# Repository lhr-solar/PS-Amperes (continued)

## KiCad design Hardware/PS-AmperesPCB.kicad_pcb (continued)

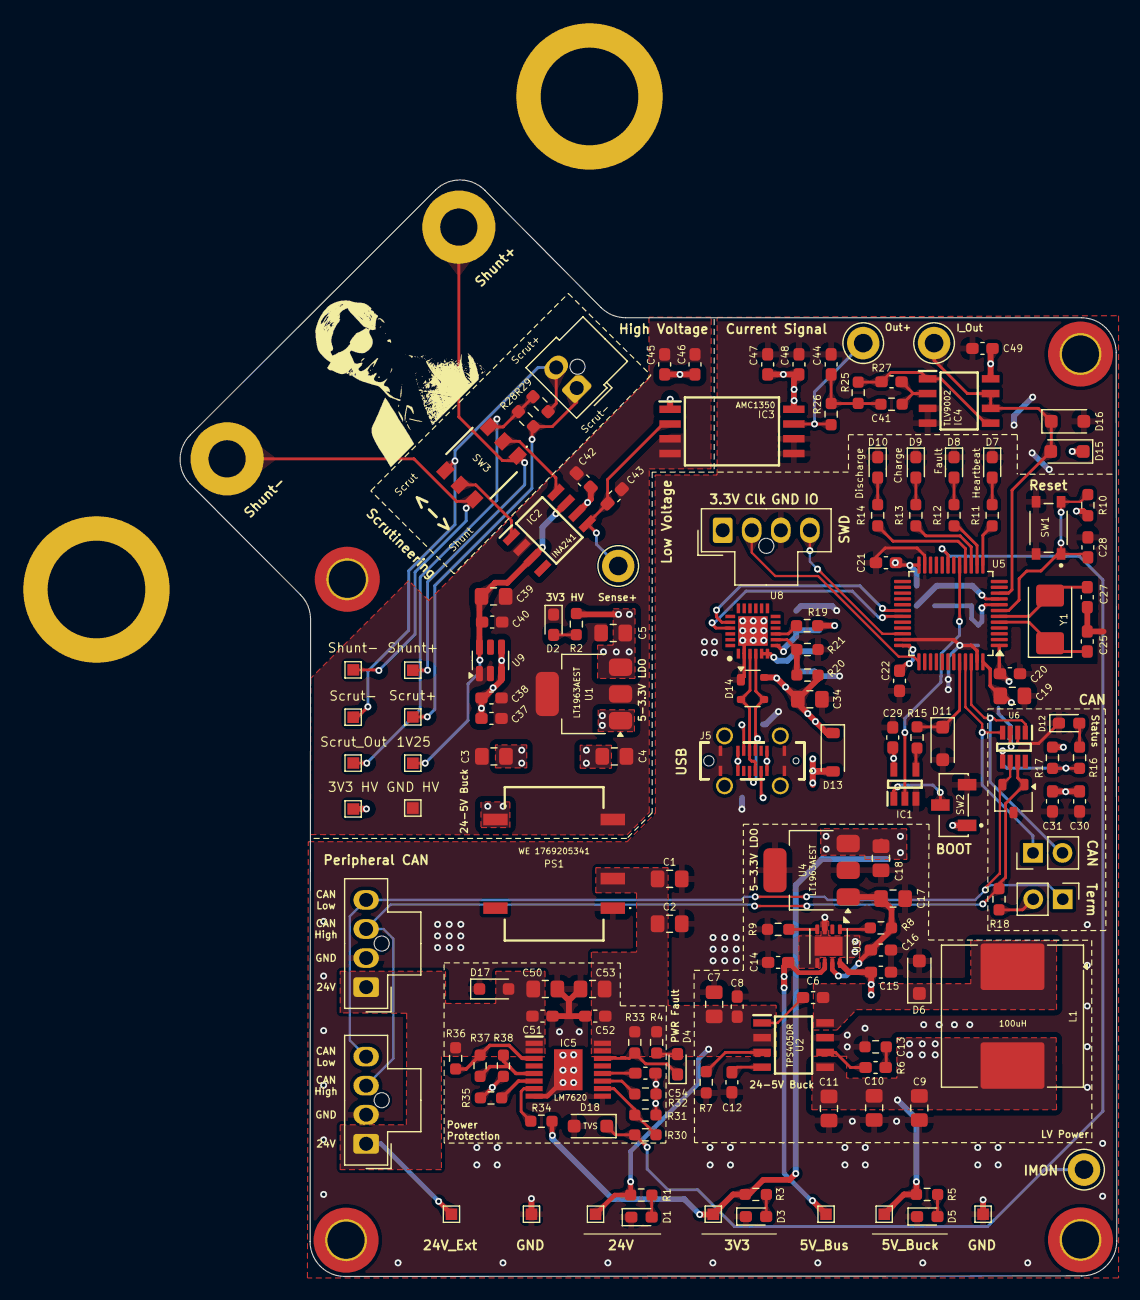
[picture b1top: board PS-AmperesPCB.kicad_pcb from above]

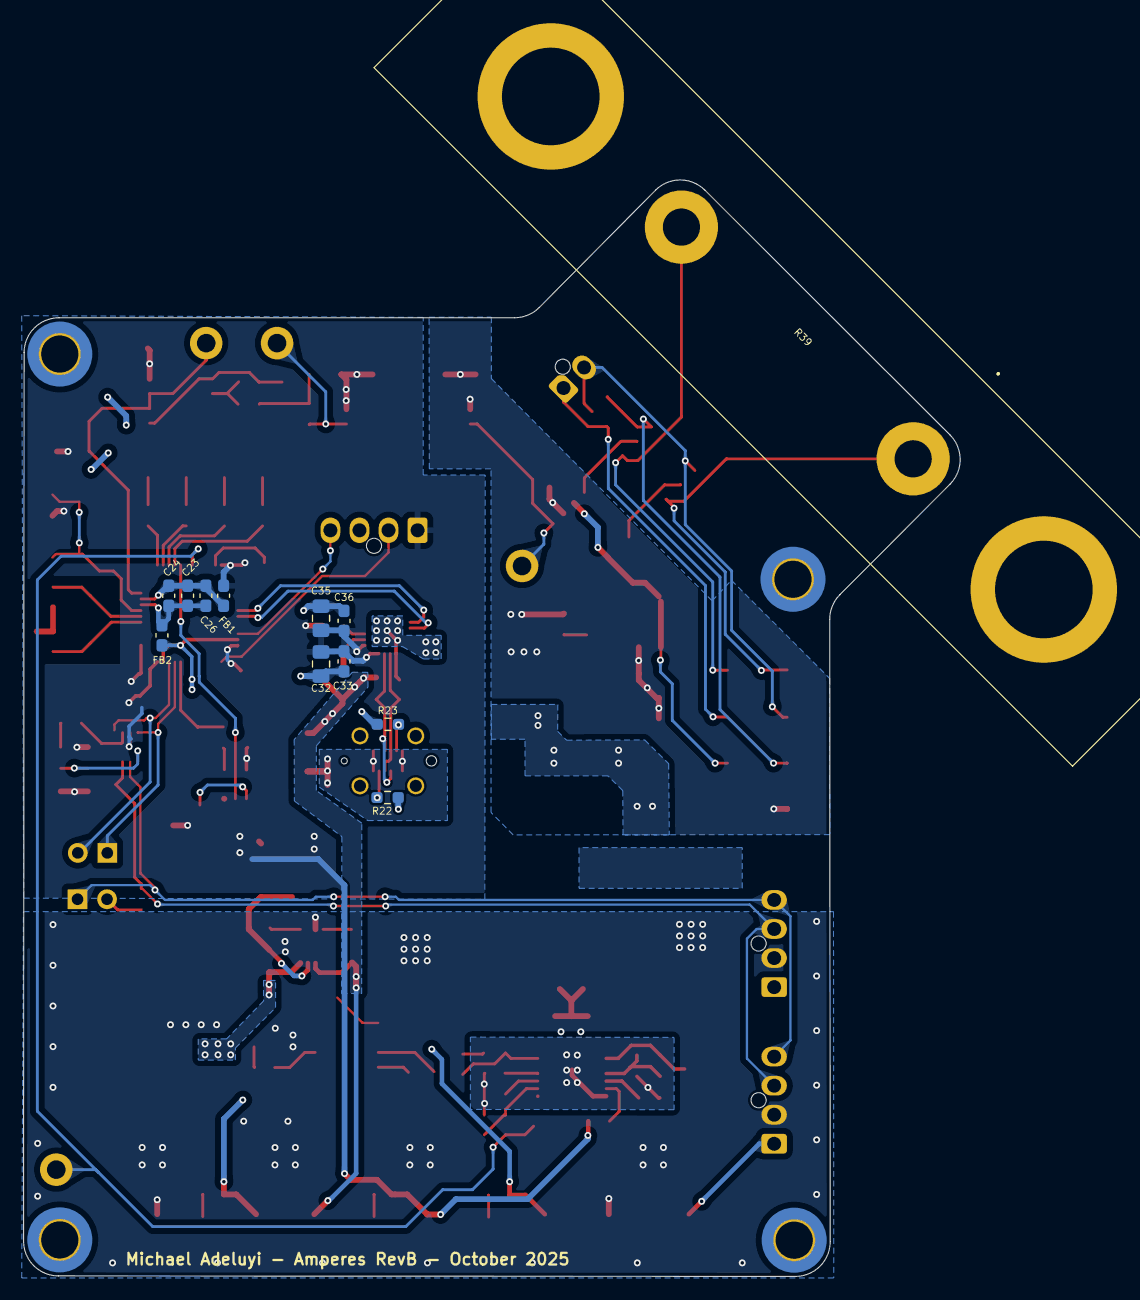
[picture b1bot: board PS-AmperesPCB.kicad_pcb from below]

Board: 2 copper layers, 80.6 x 94.4 mm, 164 parts (13 on the bottom side), 82 nets.

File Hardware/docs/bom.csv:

"Reference","Value","Footprint","Qty","p/n"
"C1,C2,C19,C32,C35","4.7uF","Capacitor_SMD:C_0805_2012Metric_Pad1.18x1.45mm_HandSolder","5",""
"C3,C4,C5,C7,C9,C10,C11,C17,C18,C34,C39,C50,C53","10uF","Capacitor_SMD:C_0805_2012Metric_Pad1.18x1.45mm_HandSolder","13",""
"C6,C14,C15,C29,C33,C36,C37,C40,C42,C49","0.1uF","Capacitor_SMD:C_0603_1608Metric_Pad1.08x0.95mm_HandSolder","10",""
"C8,C16,C38,C41,C46,C47,C51,C52","1uF","Capacitor_SMD:C_0603_1608Metric_Pad1.08x0.95mm_HandSolder","8",""
"C12","10nF","Capacitor_SMD:C_0603_1608Metric_Pad1.08x0.95mm_HandSolder","1",""
"C13","3.3nF","Capacitor_SMD:C_0603_1608Metric_Pad1.08x0.95mm_HandSolder","1",""
"C20,C21,C22,C23,C24,C26,C28,C30,C31,C45,C48,C54","100nF","Capacitor_SMD:C_0603_1608Metric_Pad1.08x0.95mm_HandSolder","12",""
"C25,C27","12p","Capacitor_SMD:C_0603_1608Metric_Pad1.08x0.95mm_HandSolder","2",""
"C43","1nF","Capacitor_SMD:C_0603_1608Metric_Pad1.08x0.95mm_HandSolder","1",""
"C44","7.5uF","Capacitor_SMD:C_0603_1608Metric_Pad1.08x0.95mm_HandSolder","1",""
"D1,TP3","24V","LED_SMD:LED_0603_1608Metric_Pad1.05x0.95mm_HandSolder,TestPoint:TestPoint_Pad_1.0x1.0mm","2",""
"D2","3.3V HV","LED_SMD:LED_0603_1608Metric_Pad1.05x0.95mm_HandSolder","1",""
"D3","3.3V","LED_SMD:LED_0603_1608Metric_Pad1.05x0.95mm_HandSolder","1",""
"D4","PFLT","LED_SMD:LED_0603_1608Metric_Pad1.05x0.95mm_HandSolder","1",""
"D5","BUCK","LED_SMD:LED_0603_1608Metric_Pad1.05x0.95mm_HandSolder","1",""
"D6","MBR230S1F","Diode_SMD:D_SOD-123F","1",""
"D7","Heartbeat","LED_SMD:LED_0603_1608Metric_Pad1.05x0.95mm_HandSolder","1",""
"D8","Fault","LED_SMD:LED_0603_1608Metric_Pad1.05x0.95mm_HandSolder","1",""
"D9","Charge","LED_SMD:LED_0603_1608Metric_Pad1.05x0.95mm_HandSolder","1",""
"D10","Discharge","LED_SMD:LED_0603_1608Metric_Pad1.05x0.95mm_HandSolder","1",""
"D11,D15,D16,D17,D18","TVS","Diode_SMD:D_SOD-123F,Diode_SMD:D_SOD-323_HandSoldering","5",""
"D12","CAN Status","LED_SMD:LED_0603_1608Metric_Pad1.05x0.95mm_HandSolder","1",""
"D13","1N5819HW","Diode_SMD:D_SOD-123","1",""
"D14","SP0503BAHT","Package_TO_SOT_SMD:SOT-143","1",""
"FB1,FB2","FerriteBead","Capacitor_SMD:C_0603_1608Metric_Pad1.08x0.95mm_HandSolder","2",""
"H1","M1","MountingHole:MountingHole_3.2mm_M3_DIN965_Pad_TopBottom","1",""
"H2","M3","MountingHole:MountingHole_3.2mm_M3_DIN965_Pad_TopBottom","1",""
"H3","M2","MountingHole:MountingHole_3.2mm_M3_DIN965_Pad_TopBottom","1",""
"H4","M4","MountingHole:MountingHole_3.2mm_M3_DIN965_Pad_TopBottom","1",""
"IC1","SN74AHC1G32DBVR","Parts:SN74AHC1G32DBVR","1",""
"IC2","INA241A4IDR","Parts:INA241A5IDR","1",""
"IC3","AMC1350DWVR","Parts:AMC1350DWVR","1",""
"IC4","TLV9002QDRQ1","Parts:TLV9002QDRQ1","1",""
"IC5","LM76202QPWPRQ1","UTSVT_Power:LM76202QPWPRQ1","1",""
"J1,J2","PeripheralCAN","UTSVT_Connectors:Molex_Nano-Fit_105309-xx04_1x04_P2.50mm_Vertical","2",""
"J3","SWD","Connector_Molex:Molex_Nano-Fit_105309-xx04_1x04_P2.50mm_Vertical","1",""
"J4","Conn_01x02_Pin","Connector_PinHeader_2.54mm:PinHeader_1x02_P2.54mm_Vertical","1",""
"J5","USB4120-03-C","Parts:USB412003C","1",""
"J6","Scrut Conn","Connector_Molex:Molex_Nano-Fit_105309-xx02_1x02_P2.50mm_Vertical","1",""
"JP1","Termination","Connector_PinHeader_2.54mm:PinHeader_1x02_P2.54mm_Vertical","1",""
"L1","100uH","Inductor_SMD:L_Coilcraft_MSS1246-XXX","1",""
"LOGO1","logo placeholder","UTSVT_Logos:LHRs_LOGO","1",""
"LOGO2","Dr. Hallock","UTSVT_Logos:Hallock_Image_Tiny","1",""
"PS1","1769205341","Parts:WE_1769205341","1",""
"R1,R4,R27","4.3k","Resistor_SMD:R_0603_1608Metric_Pad0.98x0.95mm_HandSolder","3",""
"R2,R3,R11,R12,R13,R14,R16,R18","120","Resistor_SMD:R_0603_1608Metric_Pad0.98x0.95mm_HandSolder","8",""
"R5","768","Resistor_SMD:R_0603_1608Metric_Pad0.98x0.95mm_HandSolder","1",""
"R6","16k","Resistor_SMD:R_0603_1608Metric_Pad0.98x0.95mm_HandSolder","1",""
"R7","ROSC","Resistor_SMD:R_0603_1608Metric_Pad0.98x0.95mm_HandSolder","1",""
"R8,R10,R15,R17,R32,R33,R34","10k","Resistor_SMD:R_0603_1608Metric_Pad0.98x0.95mm_HandSolder","7",""
"R9","332","Resistor_SMD:R_0603_1608Metric_Pad0.98x0.95mm_HandSolder","1",""
"R19","1k","Resistor_SMD:R_0603_1608Metric_Pad0.98x0.95mm_HandSolder","1",""
"R20","22k","Resistor_SMD:R_0603_1608Metric_Pad0.98x0.95mm_HandSolder","1",""
"R21","47k","Resistor_SMD:R_0603_1608Metric_Pad0.98x0.95mm_HandSolder","1",""
"R22,R23","5.1k","Resistor_SMD:R_0603_1608Metric_Pad0.98x0.95mm_HandSolder","2",""
"R25","8.2k","Resistor_SMD:R_0603_1608Metric_Pad0.98x0.95mm_HandSolder","1",""
"R26","3.3k","Resistor_SMD:R_0603_1608Metric_Pad0.98x0.95mm_HandSolder","1",""
"R28","34k","Resistor_SMD:R_0603_1608Metric_Pad0.98x0.95mm_HandSolder","1",""
"R29","51","Resistor_SMD:R_0603_1608Metric_Pad0.98x0.95mm_HandSolder","1",""
"R30","100k","Resistor_SMD:R_0603_1608Metric_Pad0.98x0.95mm_HandSolder","1",""
"R31","19k","Resistor_SMD:R_0603_1608Metric_Pad0.98x0.95mm_HandSolder","1",""
"R35","402k","Resistor_SMD:R_0603_1608Metric_Pad0.98x0.95mm_HandSolder","1",""
"R36","45.3k","Resistor_SMD:R_0603_1608Metric_Pad0.98x0.95mm_HandSolder","1",""
"R37","590","Resistor_SMD:R_0603_1608Metric_Pad0.98x0.95mm_HandSolder","1",""
"R38","2.1k","Resistor_SMD:R_0603_1608Metric_Pad0.98x0.95mm_HandSolder","1",""
"R39","WSBS8518L2500JTP3","Parts:WSBS8518L2500JKM4","1",""
"SW1","RST","Parts:SW_TL3365AF180QG","1",""
"SW2","BOOT","Parts:SW_CJS-1200TA","1",""
"SW3","Scrut Select","Parts:CAS220TB","1",""
"TP1","TP_Current","TestPoint:TestPoint_Keystone_5005-5009_Compact","1",""
"TP2","24V_Ext","TestPoint:TestPoint_Pad_1.0x1.0mm","1",""
"TP4","3V3_HV","TestPoint:TestPoint_Pad_1.0x1.0mm","1",""
"TP5","3V3","TestPoint:TestPoint_Pad_1.0x1.0mm","1",""
"TP6","5V_BK","TestPoint:TestPoint_Pad_1.0x1.0mm","1",""
"TP7","5V_USB","TestPoint:TestPoint_Pad_1.0x1.0mm","1",""
"TP8,TP15","GND","TestPoint:TestPoint_Pad_1.0x1.0mm","2",""
"TP9","GND HV","TestPoint:TestPoint_Pad_1.0x1.0mm","1",""
"TP10","SHUNT+","TestPoint:TestPoint_Pad_1.0x1.0mm","1",""
"TP11","SHUNT-","TestPoint:TestPoint_Pad_1.0x1.0mm","1",""
"TP12","V_In+","TestPoint:TestPoint_Pad_1.0x1.0mm","1",""
"TP13","V_Out+","TestPoint:TestPoint_Pad_1.0x1.0mm","1",""
"TP14","V_In-","TestPoint:TestPoint_Pad_1.0x1.0mm","1",""
"TP16","1V25","TestPoint:TestPoint_Pad_1.0x1.0mm","1",""
"TP17","Sense+","TestPoint:TestPoint_Keystone_5005-5009_Compact","1",""
"TP18","Out+","TestPoint:TestPoint_Keystone_5005-5009_Compact","1",""
"TP19","IMON","TestPoint:TestPoint_Keystone_5005-5009_Compact","1",""
"U1,U4","LT1963AEST-3.3#TRPBF","Package_TO_SOT_SMD:SOT-223-3_TabPin2","2",""
"U2","TPS5405DR","UTSVT_Power:TPS5405DR","1",""
"U3","TPS2115ADRBR","Package_SON:VSON-8-1EP_3x3mm_P0.65mm_EP1.65x2.4mm","1",""
"U5","STM32L431CBTx","Package_QFP:LQFP-48_7x7mm_P0.5mm","1",""
"U6","TCAN337","UTSVT_ICs:TCAN337DCNR","1",""
"U7","CDSOT23-T24CAN","UTSVT_ICs:CDSOT23-T24CAN","1",""
"U8","CP2102N-A02-GQFN24","UTSVT_ICs:CP2102N-A02-GQFN24","1",""
"U9","REF35125QDBVR","Package_TO_SOT_SMD:SOT-23-6","1",""
"Y1","8M","Crystal:Crystal_SMD_Abracon_ABM3-2Pin_5.0x3.2mm","1",""

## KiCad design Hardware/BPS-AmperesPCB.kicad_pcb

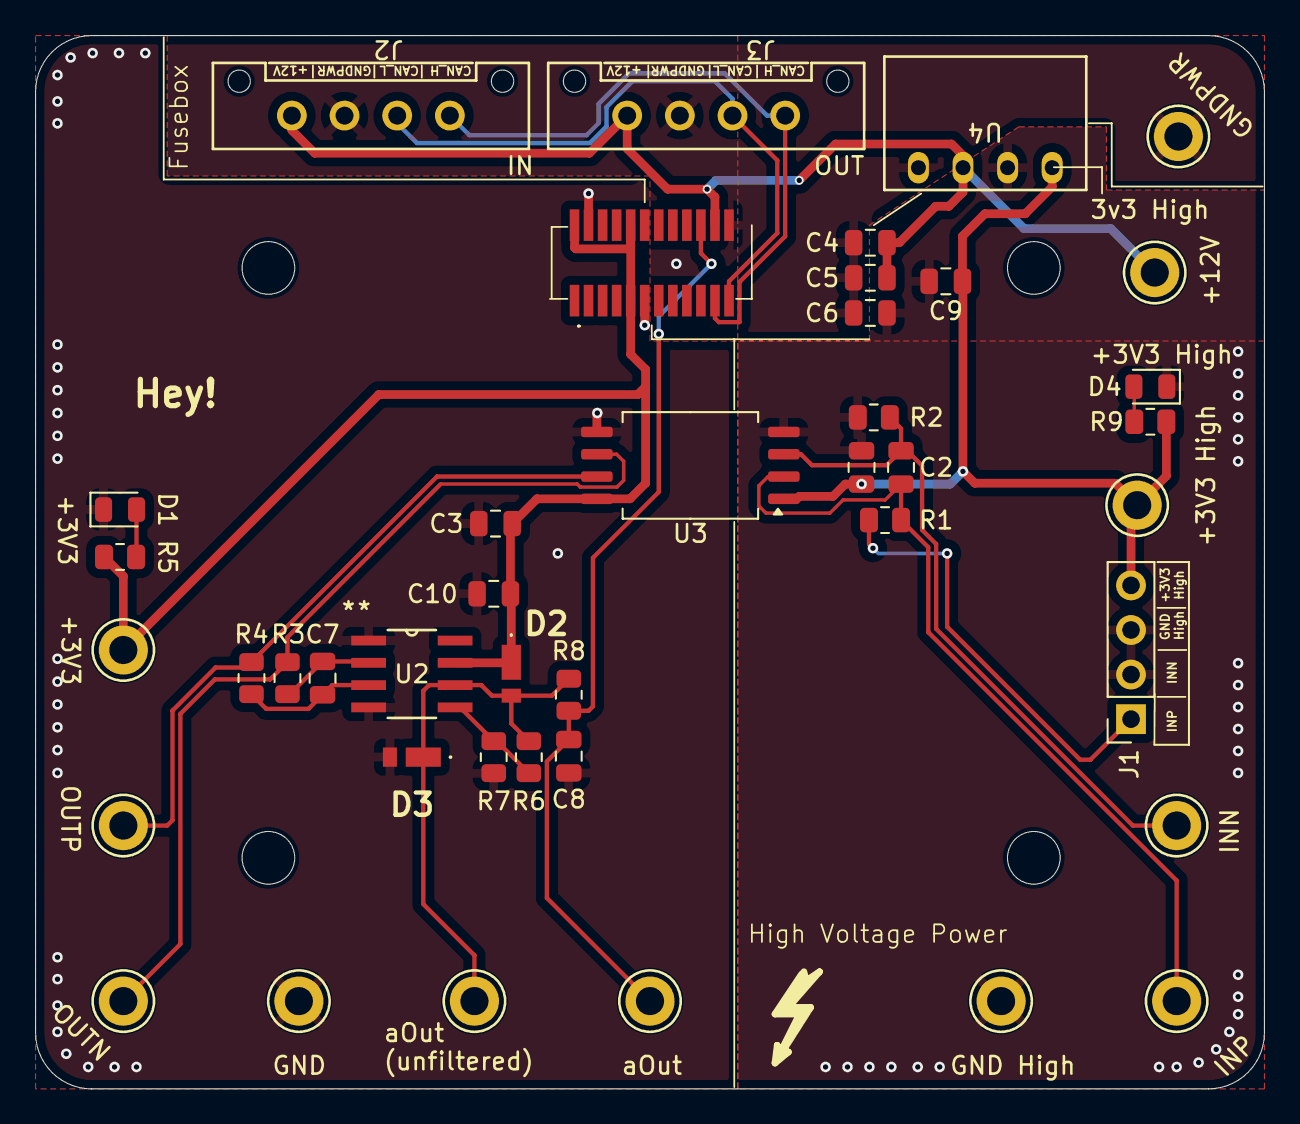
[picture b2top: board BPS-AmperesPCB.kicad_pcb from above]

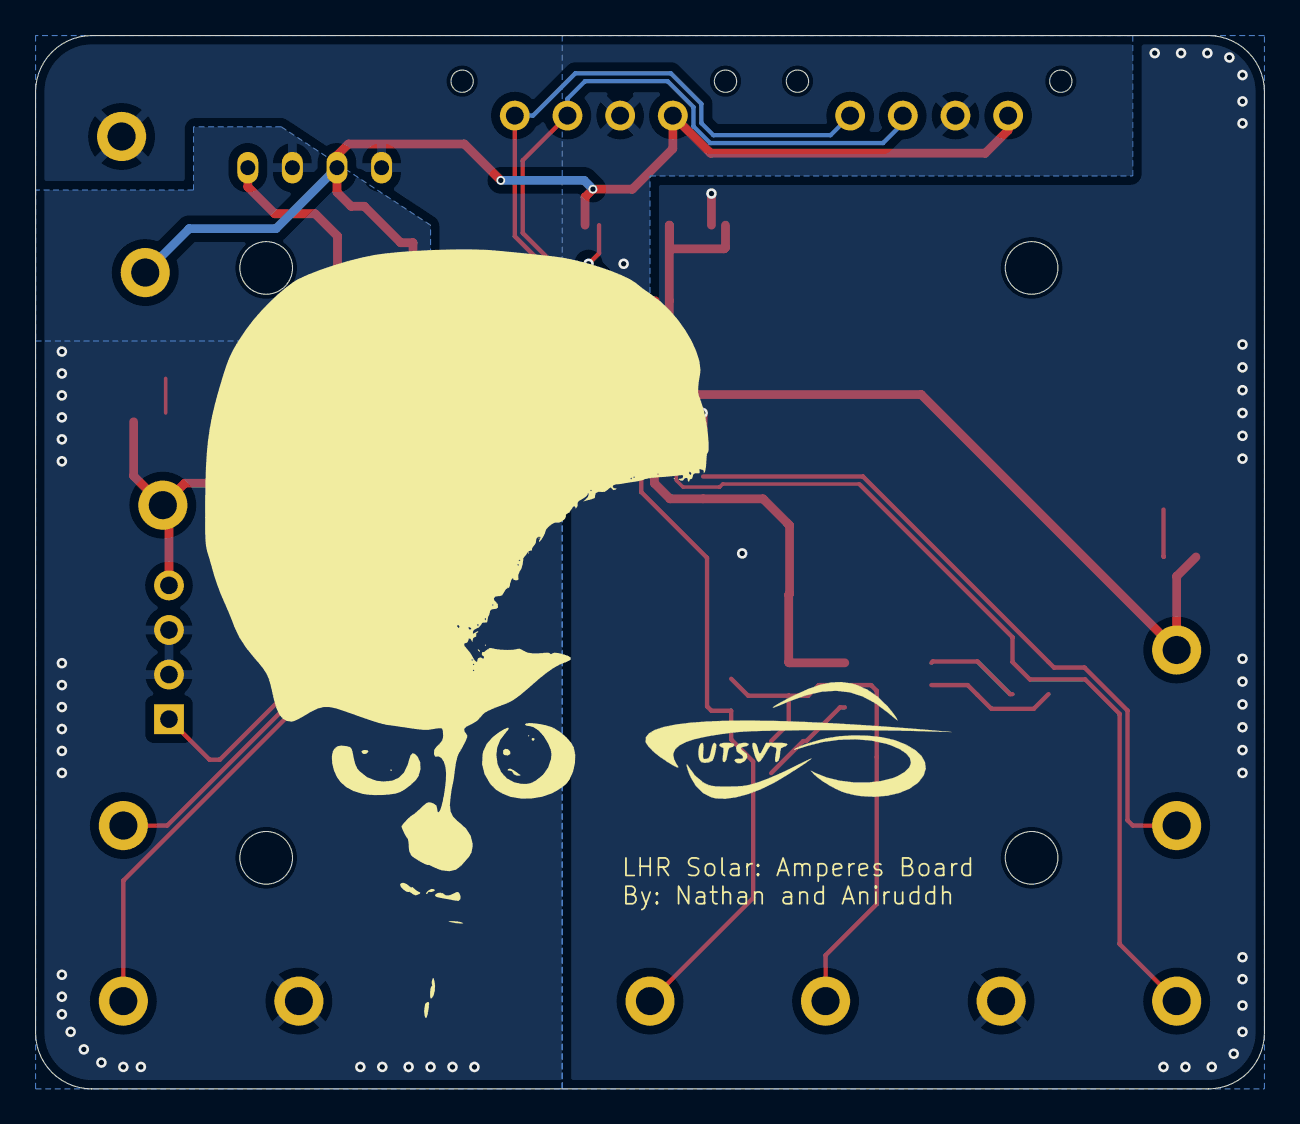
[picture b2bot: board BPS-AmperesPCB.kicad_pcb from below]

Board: 2 copper layers, 70.0 x 60.0 mm, 44 parts (2 on the bottom side), 20 nets.

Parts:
+3V3, +3V3H1, +12V1: TestPoint; TestPoint_Keystone_5005-5009_Compact
C1, C3, C10: 1uF; C_0805_2012Metric
C2, C7, C8: 2.2uF; C_0805_2012Metric
C4: 1n; C_0805_2012Metric
C5: 10u; C_0805_2012Metric
C6: 2.2n; C_0805_2012Metric
C9: 10uF; C_0805_2012Metric
D1, D4: PowerOn; LED_0805_2012Metric
D2, D3: RBE01VYM6AFHTR
GND1: TestPoint; TestPoint_Keystone_5005-5009_Compact
GNDH1: TestPoint; TestPoint_Keystone_5005-5009_Compact
GNDPWR1: TestPoint; TestPoint_Keystone_5005-5009_Compact
INN1: TestPoint; TestPoint_Keystone_5005-5009_Compact
INP1: TestPoint; TestPoint_Keystone_5005-5009_Compact
J1: Conn_01x04; PinSocket_1x04_P2.54mm_Vertical
J2, J3: PeripheralCANConnector; Molex_MicroFit3.0_1x4xP3.00mm_PolarizingPeg_Vertical
LOGO1: aniMegamind
LOGO2: solarlogo; UTSVT_Logo_Symbol
OUTN1: TestPoint; TestPoint_Keystone_5005-5009_Compact
OUTP1: TestPoint; TestPoint_Keystone_5005-5009_Compact
R1, R2, R3, R4: 2.4k; R_0805_2012Metric
R5, R9: 1.5k; R_0805_2012Metric
R6: 12k; R_0805_2012Metric
R7: 1k; R_0805_2012Metric
R8: 4.8k; R_0805_2012Metric
U1: PeripheralSOM
U2: INA145UA/2K5; D8
U3: AMC1300BDWV; SOIC-8_7.5x5.85mm_P1.27mm
U4: RO-123.3S_HP; RI3_DC_Converter
VOut1: TestPoint; TestPoint_Keystone_5005-5009_Compact
aOut1: TestPoint; TestPoint_Keystone_5005-5009_Compact

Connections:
+3V3: +3V3.1, C3.1, C10.1, D2.1 (K), R5.1, U1.2 (+3.3V), U1.9 (+3.3V), U1.10 (VDDA(3.3V)), U2.7 (V+), U3.8 (V+)
+3V3 High: +3V3H1.1, C1.1, C9.1, J1.4, R9.1, U3.1 (V+), U4.4 (+Vout)
+12V: +12V1.1, C4.1, C5.1, J2.1 (12V), J3.1 (12V), U1.22 (+12V_In), U4.2 (+Vin)
/INN: C2.2, INN1.1, R2.1, U3.3 (-)
/INP: C2.1, INP1.1, R1.1, U3.2 (+)
/OUTN: OUTN1.1, R3.2, U3.6 (-)
/OUTP: OUTP1.1, R4.2, U3.7 (+)
/aOut: C8.1, R8.1, U1.20 (PA1(ADC)), aOut1.1
GND: C3.2, C8.2, C10.2, D1.1 (K), D3.2 (A), GND1.1, R7.2, U1.4 (GND), U1.11 (GND), U2.1 (REF), U2.4 (V-), U3.5 (V-)
GND High: C1.2, C6.2, C9.2, D4.1 (K), GNDH1.1, J1.2, J1.3, R2.2, U3.4 (V-), U4.3 (-Vout)
GNDPWR: C4.2, C5.2, C6.1, GNDPWR1.1, J2.2 (GNDPWR), J3.2 (GNDPWR), U1.24 (GNDPWR), U4.1 (-Vin)
unnamed: D1.2 (A), R5.2
unnamed: D2.2 (A), D3.1 (K), R6.1, R8.2, U2.6 (VO), VOut1.1
unnamed: D4.2 (A), R9.2
unnamed: J1.1, R1.2
unnamed: J2.3 (CAN_H), J3.3 (CAN_H), U1.23 (CAN_H)
unnamed: J2.4 (CAN_L), J3.4 (CAN_L), U1.21 (CAN_L)
unnamed: R6.2, R7.1, U2.5 (RG)
unnamed: C7.2, R4.1, U2.3 (V+IN)
unnamed: C7.1, R3.1, U2.2 (V-IN)

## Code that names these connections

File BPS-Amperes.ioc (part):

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Mcu.Name=STM32L431C(B-C)Tx
Mcu.Package=LQFP48
Mcu.UserName=STM32L431CBTx
PA0.Signal=ADCx_IN5
PA10.Mode=Asynchronous
PA10.Signal=USART1_RX
PA13\ (JTMS-SWDIO).Mode=Serial_Wire
PA13\ (JTMS-SWDIO).Signal=SYS_JTMS-SWDIO
PA14\ (JTCK-SWCLK).Mode=Serial_Wire
PA14\ (JTCK-SWCLK).Signal=SYS_JTCK-SWCLK
PA3.Signal=GPIO_Output
PA4.Signal=GPIO_Output
PA5.Signal=GPIO_Output
PA6.Signal=GPIO_Output
PA9.Mode=Asynchronous
PA9.Signal=USART1_TX
PB8.Mode=CAN_Activate
PB8.Signal=CAN1_RX
PB9.Mode=CAN_Activate
PB9.Signal=CAN1_TX
PH0-OSC_IN\ (PH0).Mode=HSE-External-Oscillator
PH0-OSC_IN\ (PH0).Signal=RCC_OSC_IN
PH1-OSC_OUT\ (PH1).Mode=HSE-External-Oscillator
PH1-OSC_OUT\ (PH1).Signal=RCC_OSC_OUT
RCC.HSE_VALUE=8000000
board=custom

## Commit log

2025-02-01 layout draft
2025-02-01 new footprints
2025-02-01 working layout
2025-02-01 tag team
2025-02-01 ignore working files
2025-02-01 changed layout
2025-02-01 reviewable
2025-02-08 reviewable part 2
2025-02-08 decor fancy
2025-02-08 tada
2025-02-11 bored so i did lhr
2025-02-15 fixed outp and outn flip smh
2025-02-15 edits 1.0 still have to change some stuff Lakshay
2025-02-17 gerb'd all over da place
2025-04-12 Amperes v1.0 (#1)
    * new parts
    * Testpoints and Math
    * Daisy Chain CAN Connectors
    * layout draft
    * new footprints
    * working layout
2025-04-12 stuff
2025-04-12 added Embedded sharepoint
2025-04-12 gitignore, added placeholder files to check compilation (it compiles hooray)
2025-04-13 started outline for driver
2025-04-26 first iteration of amperes code, testing init and get_reading using main
2025-05-26 initial sch change, added PSOM components
2025-05-28 migrated to KiCad 9
2025-05-28 replaced UTSVT with KiCAD-Bild submodule
2025-05-28 updated symbol, footprint paths
2025-05-28 mcu and CAN added, missing Amperes DC-DC sym / footprint
2025-05-29 added RO-123.3S_HP part but it might not be the right one
2025-06-06 addressed comments
2025-06-08 isolated 3v3 done?
2025-06-11 finished? power on sch
2025-06-11 added MX cube pinout screenshot
2025-06-21 ADC init seems to work, CAN is set up (not tested)
2025-06-21 power
2025-08-21 added 24V buck, bypass caps, more LEDs; started scrutineering circuit and bidirectional current sense
2025-08-23 organization, updated submodule
2025-08-23 finally back - deleted hardware stuff - better organization (Tasks folder, common.h) - will address more comments later
2025-08-23 small tweaks
2025-08-24 updated Amperes Init
2025-08-24 shunt to current sense to isolation done?? need to select values
2025-08-30 new isolated amp, filter stage; need to select values
2025-08-30 lowk got some filter values from chat PLEASE PLEASE PLEASE VERIFY LATER
2025-08-31 plz review
2025-08-31 comments
2025-09-02 changed input into AMC1350, added unity gain buffer
2025-09-04 added LEDs, changed LDO, still need to address other comments
2025-09-04 is this how you TVS
2025-09-06 changed to TI generated filter
2025-09-06 set reference voltage for current sense
2025-09-06 scrutineering should be done, started on USB
2025-09-06 copied USB-C from psom
2025-09-06 something changed idk what though
2025-09-07 sch almost done
2025-09-07 0603 footprints
2025-09-08 dpdt switch for scrutineering
2025-09-09 24-5 buck from psom, OR gate for bootload. more sheet organization
2025-09-09 op amp
2025-09-10 changed to 2 channel op amp, stole RPP from PSOM
2025-09-11 added voltage reference, shunt model; addressed comments
2025-09-11 cleaned up parts lib, correct INA ic listed
2025-09-11 added vertical usb c
2025-09-13 renamed, added OR gate part
2025-09-13 lay out lay out
2025-09-20 changed shunt model, moved around folders; initial layout, routing soon
2025-09-20 9/20 workday: some layout stuff ye ye
2025-09-27 better layout, started routing
2025-09-27 board is smaller ? idk
2025-09-27 more routing later :(
2025-09-28 more routing
2025-10-02 review council
2025-10-04 silkscreen work
2025-10-04 added models
2025-10-04 i don't know what I changed
2025-10-07 more silkscreen, addressed some comments
2025-10-08 more comments addressed
2025-10-08 drc drc
2025-10-09 updated some component part nums
2025-10-11 new dpdt switch, layout done
2025-10-11 generated production stuff
2025-10-11 updated production files again
2025-10-12 added a 3d model nothing too crazy i think
2025-10-12 updated step file
2025-10-25 docs, bom pushed
2025-10-25 added bom
2025-10-25 bom again
2025-10-25 adc blinky
2025-11-01 updated amperes docs
2025-11-01 adc to current conversion, need to test
2025-11-01 confirmed adc current reading hooray
2025-11-01 started CAN stuff
2025-11-04 RevB (#2)
    * initial sch change, added PSOM components
    * migrated to KiCad 9
    * replaced UTSVT with KiCAD-Bild submodule
    * updated symbol, footprint paths
    * mcu and CAN added, missing Amperes DC-DC sym / footprint
    * added RO-123.3S_HP part but it might not be the right one
